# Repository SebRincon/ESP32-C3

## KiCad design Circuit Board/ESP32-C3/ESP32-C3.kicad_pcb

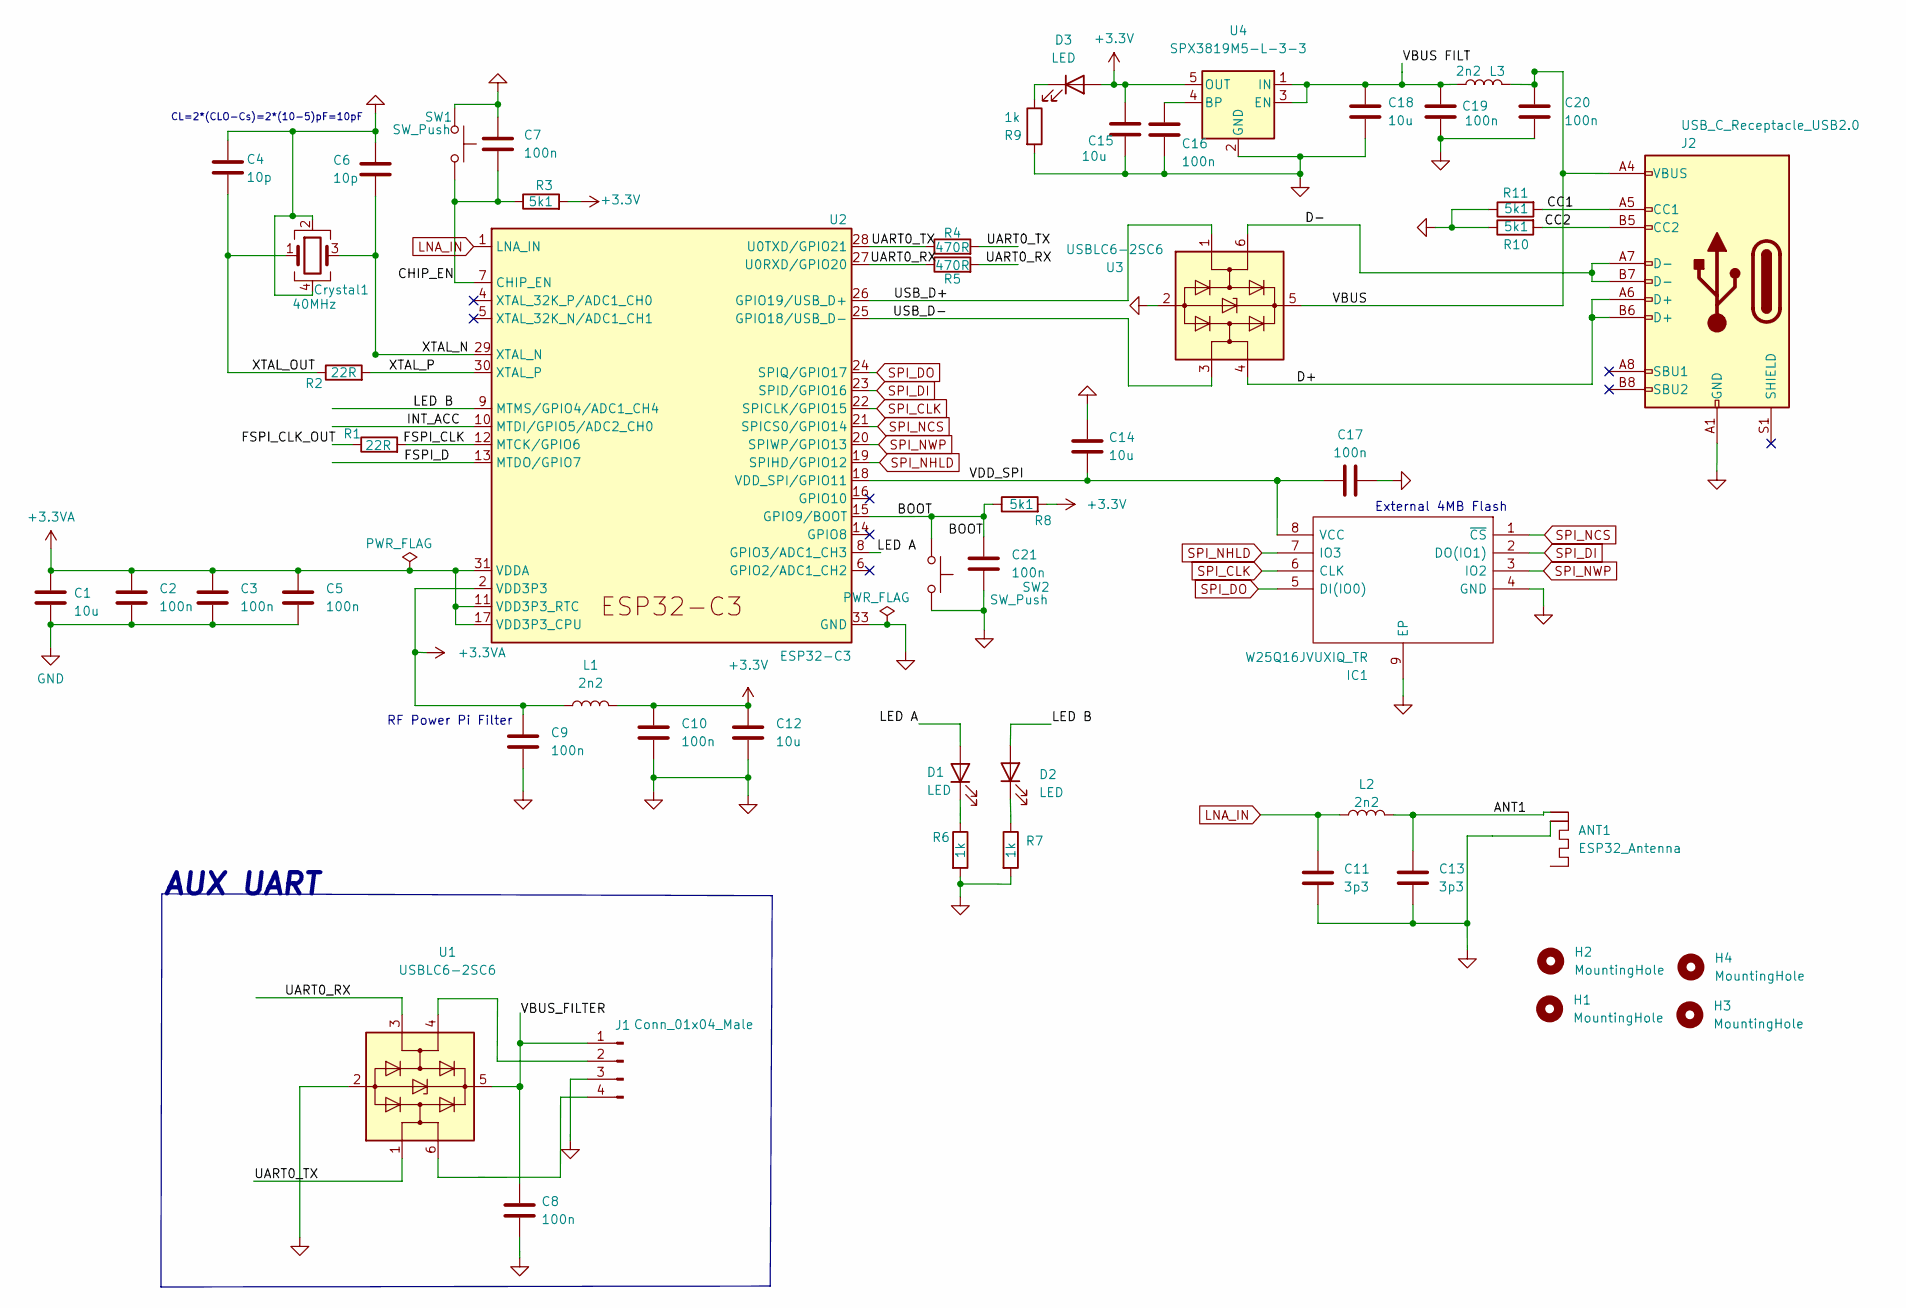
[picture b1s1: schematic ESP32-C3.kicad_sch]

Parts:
ANT1: ESP32_Antenna; ESPRESSIF_ESP32_MIFA_2.4GHz_Right
C1, C12, C14, C15, C18: 10u; C_0603_1608Metric
C2, C3, C5, C7, C8, C9, C10, C16, C17, C19, C20, C21: 100n; C_0402_1005Metric
C4, C6: 10p; C_0402_1005Metric
C11, C13: 3p3; C_0402_1005Metric
Crystal1: 40MHz; Crystal_SMD_3225-4Pin_3.2x2.5mm_HandSoldering
D1, D2, D3: LED; LED_0603_1608Metric
H1, H2, H3, H4: MountingHole; MountingHole_2.2mm_M2
IC1: W25Q16JVUXIQ_TR; SON50P300X200X60-9N; Mouser Part Number 454-W25Q16JVUXIQTR
J1: Conn_01x04_Male; PinHeader_1x04_P2.00mm_Vertical
J2: USB_C_Receptacle_USB2.0; USB_C_Receptacle_HRO_TYPE-C-31-M-12
L1, L2, L3: 2n2; L_0603_1608Metric
R1, R2: 22R; R_0402_1005Metric
R3, R8, R10, R11: 5k1; R_0402_1005Metric
R4, R5: 470R; R_0402_1005Metric
R6, R7, R9: 1k; R_0402_1005Metric
SW1, SW2: SW_Push; SW_SPST_B3U-1000P
U1, U3: USBLC6-2SC6; SOT-23-6
U2: ESP32-C3; QFN-32-1EP_5x5mm_P0.5mm_EP3.45x3.45mm
U4: SPX3819M5-L-3-3; SOT-23-5

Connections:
+3.3V: C10.1, C12.1, C15.1, D3.2 (A), L1.2, R3.2, R8.2, U4.5 (OUT)
+3.3VA: C1.1, C2.1, C3.1, C5.1, C9.1, L1.1, U2.2 (VDD3P3), U2.3 (VDD3P3), U2.11 (VDD3P3_RTC), U2.17 (VDD3P3_CPU), U2.31 (VDDA), U2.32 (VDDA)
/ANT1: ANT1.1 (Feed), C13.1, L2.2
/BOOT: C21.1, R8.1, SW2.1, U2.15 (GPIO9/BOOT)
/CC1: J2.A5 (CC1), R11.2
/CC2: J2.B5 (CC2), R10.2
/CHIP_EN: C7.2, R3.1, SW1.2, U2.7 (CHIP_EN)
/D+: J2.A6 (D+), J2.B6 (D+), U3.4 (I/O2)
/D-: J2.A7 (D-), J2.B7 (D-), U3.6 (I/O1)
/FSPI_CLK: R1.2, U2.12 (MTCK/GPIO6)
/FSPI_CLK_OUT: R1.1
/FSPI_D: U2.13 (MTDO/GPIO7)
/INT_ACC: U2.10 (MTDI/GPIO5/ADC2_CH0)
/LED A: D1.2 (A), U2.8 (GPIO3/ADC1_CH3); also elsewhere on the board
/LED B: D2.2 (A), U2.9 (MTMS/GPIO4/ADC1_CH4); also elsewhere on the board
/UART0_RX: R5.1, R5.2, U1.3 (I/O2), U2.27 (U0RXD/GPIO20)
/UART0_TX: R4.1, R4.2, U1.1 (I/O1), U2.28 (U0TXD/GPIO21)
/USB_D+: U2.26 (GPIO19/USB_D+), U3.1 (I/O1)
/USB_D-: U2.25 (GPIO18/USB_D-), U3.3 (I/O2)
/VBUS: C20.1, J2.A4 (VBUS), J2.A9 (VBUS), J2.B4 (VBUS), J2.B9 (VBUS), L3.2, U3.5 (VBUS)
/VBUS FILT: C18.1, C19.1, L3.1, U4.1 (IN), U4.3 (EN)
/VBUS_FILTER: C8.1, J1.1, U1.5 (VBUS)
/VDD_SPI: C14.2, C17.1, IC1.8 (VCC), U2.18 (VDD_SPI/GPIO11)
/XTAL_N: C6.2, Crystal1.3, U2.29 (XTAL_N)
/XTAL_OUT: C4.2, Crystal1.1, R2.1
/XTAL_P: R2.2, U2.30 (XTAL_P)
GND: ANT1.2 (GND), C1.2, C2.2, C3.2, C4.1, C5.2, C6.1, C7.1, C8.2, C9.2, C10.2, C11.2, C12.2, C13.2, C14.1, C15.2, C16.2, C17.2, C18.2, C19.2, C20.2, C21.2, Crystal1.2, Crystal1.4, IC1.4 (GND), IC1.9 (EP), J1.3, J2.A1 (GND), J2.A12 (GND), J2.B1 (GND), J2.B12 (GND), R6.2, R7.2, R9.2, R10.1, R11.1, SW1.1, SW2.2, U1.2 (GND), U2.33 (GND), U3.2 (GND), U4.2 (GND)
LNA_IN: C11.1, L2.1, U2.1 (LNA_IN)
unnamed: C16.1, U4.4 (BP)
unnamed 29: D1.1 (K), R6.1; also elsewhere on the board
unnamed 30: D2.1 (K), R7.1; also elsewhere on the board
unnamed: D3.1 (K), R9.1
unnamed: J1.2, U1.4 (I/O2)
unnamed: J1.4, U1.6 (I/O1)
SPI_CLK: IC1.6 (CLK), U2.22 (SPICLK/GPIO15)
SPI_DI: IC1.2 (DO(IO1)), U2.23 (SPID/GPIO16)
SPI_DO: IC1.5 (DI(IO0)), U2.24 (SPIQ/GPIO17)
SPI_NCS: IC1.1 (~CS), U2.21 (SPICS0/GPIO14)
SPI_NHLD: IC1.7 (IO3), U2.19 (SPIHD/GPIO12)
SPI_NWP: IC1.3 (IO2), U2.20 (SPIWP/GPIO13)

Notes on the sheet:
RF Power Pi Filter
External 4MB Flash
AUX UART
CL=2*(CLO-Cs)=2*(10-5)pF=10pF

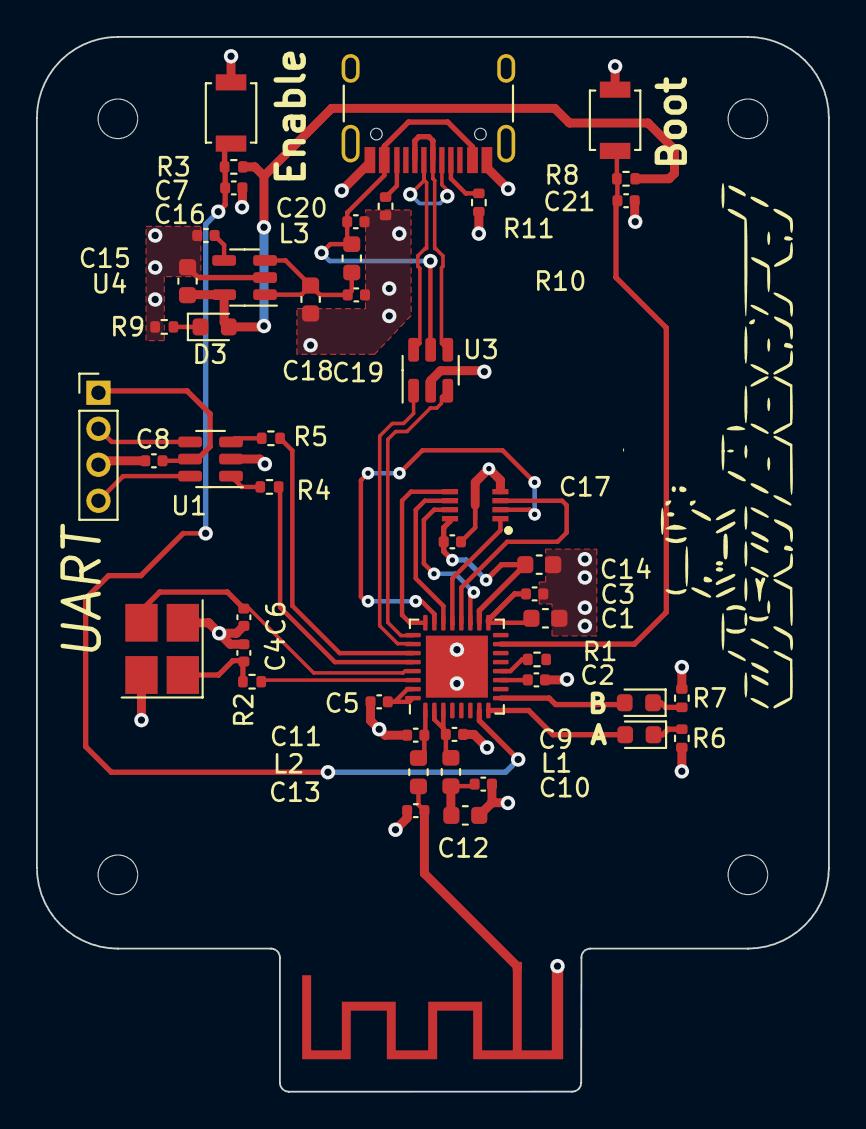
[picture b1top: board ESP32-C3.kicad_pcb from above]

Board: 2 copper layers, 44.0 x 58.6 mm, 53 parts (0 on the bottom side), 37 nets.

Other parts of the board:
A: LED; LED_0603_1608Metric
B: LED; LED_0603_1608Metric

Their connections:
/LED A: A.2 (A); also elsewhere on the board
/LED B: B.2 (A); also elsewhere on the board
unnamed 29: A.1 (K); also elsewhere on the board
unnamed 30: B.1 (K); also elsewhere on the board

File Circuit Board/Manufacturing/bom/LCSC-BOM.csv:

Qty,Reference(s),Value,Footprint,JLCPCB Part #,DigiKey #,Qty
5,"C1, C12, C14, C15, C18",10u,Capacitor_SMD:C_0603_1608Metric,C19702,,
12,"C2, C3, C5, C7, C8, C9, C10, C16, C17, C19, C20, C21",100n,Capacitor_SMD:C_0402_1005Metric,C131394,,
2,"C4, C6",10p,Capacitor_SMD:C_0402_1005Metric,C106199,,
2,"C11, C13",3p3,Capacitor_SMD:C_0402_1005Metric,C1565,,
1,Crystal1,40MHz,Crystal:Crystal_SMD_3225-4Pin_3.2x2.5mm_HandSoldering,C5765968,,
3,"D1, D2, D3",LED,LED_SMD:LED_0603_1608Metric,C84267,,
1,IC1,W25Q16JVUXIQ_TR,W25Q16JVUXIQ_TR:SON50P300X200X60-9N,C2843335,256-W25Q16JVUXIQTRCT-ND,
1,J1,Conn_01x04_Male,Connector_PinHeader_2.00mm:PinHeader_1x04_P2.00mm_Vertical,C541858,,
1,J2,USB_C_Receptacle_USB2.0,Connector_USB:USB_C_Receptacle_HRO_TYPE-C-31-M-12,C165948,,
3,"L1, L2, L3",2n2,Inductor_SMD:L_0603_1608Metric,C280268,553-BSCH001608082N2S00CT-ND,
2,"R1, R2",22R,Resistor_SMD:R_0402_1005Metric,C25092,1292-WR04X220JTLCT-ND,100
4,"R3, R8, R10, R11",5k1,Resistor_SMD:R_0402_1005Metric,C25905,311-5.10KLRCT-ND,100
2,"R4, R5",470R,Resistor_SMD:R_0402_1005Metric,C114877,1292-WR04X4700FTLCT-ND,100
3,"R6, R7, R9",1k,Resistor_SMD:R_0402_1005Metric,C25543,RMCF0402FT1K00CT-ND,100
2,"SW1, SW2",SW_Push,Button_Switch_SMD:SW_SPST_B3U-1000P,C231329,SW1020CT-ND,100
2,"U1, U3",USBLC6-2SC6,Package_TO_SOT_SMD:SOT-23-6,C7519,497-5235-1-ND,100
1,U2,ESP32-C3,Package_DFN_QFN:QFN-32-1EP_5x5mm_P0.5mm_EP3.45x3.45mm,C2838500,1904-ESP32-C3CT-ND,100
1,U4,SPX3819M5-L-3-3,Package_TO_SOT_SMD:SOT-23-5,C9055,1016-1873-1-ND,100

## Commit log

2023-02-06 Inital Commit
2023-02-06 Added decoupling capacitors & pi filter
2023-02-06 Added the crystal oscillator
2023-02-06 Added power on switch
2023-02-07 Added external flash memory
2023-02-07 Exposed General Purpose SPI & LED
2023-02-07 Added UART Pinout
2023-02-08 Added power regulator for USB C connector
2023-02-15 Added Auxiliary UART Pins
2023-02-19 Added boot loader switch
2023-02-22 Added RF antenna circuit
2023-02-22 Added RF antenna inductor
2023-02-22 Added LED circuits
2023-02-23 Added comments
2023-02-23 Annotated designators
2023-02-23 Correct ERC errors
2023-05-13 Started PCB routing
2023-05-15 Finished PCB Layout v1.0
2023-05-15 Updated PCB Info
2023-05-15 Generated BOM
2023-05-15 Quick PCB Alignment
2023-05-15 PNP Placement File
2023-05-15 Gerberfile Creation
2023-05-15 Updated USB-C Silkscreen issue
2023-05-16 Gerbers ZIP + BOM CSV
2023-05-16 Preference Changes
2023-05-16 Readme Image
